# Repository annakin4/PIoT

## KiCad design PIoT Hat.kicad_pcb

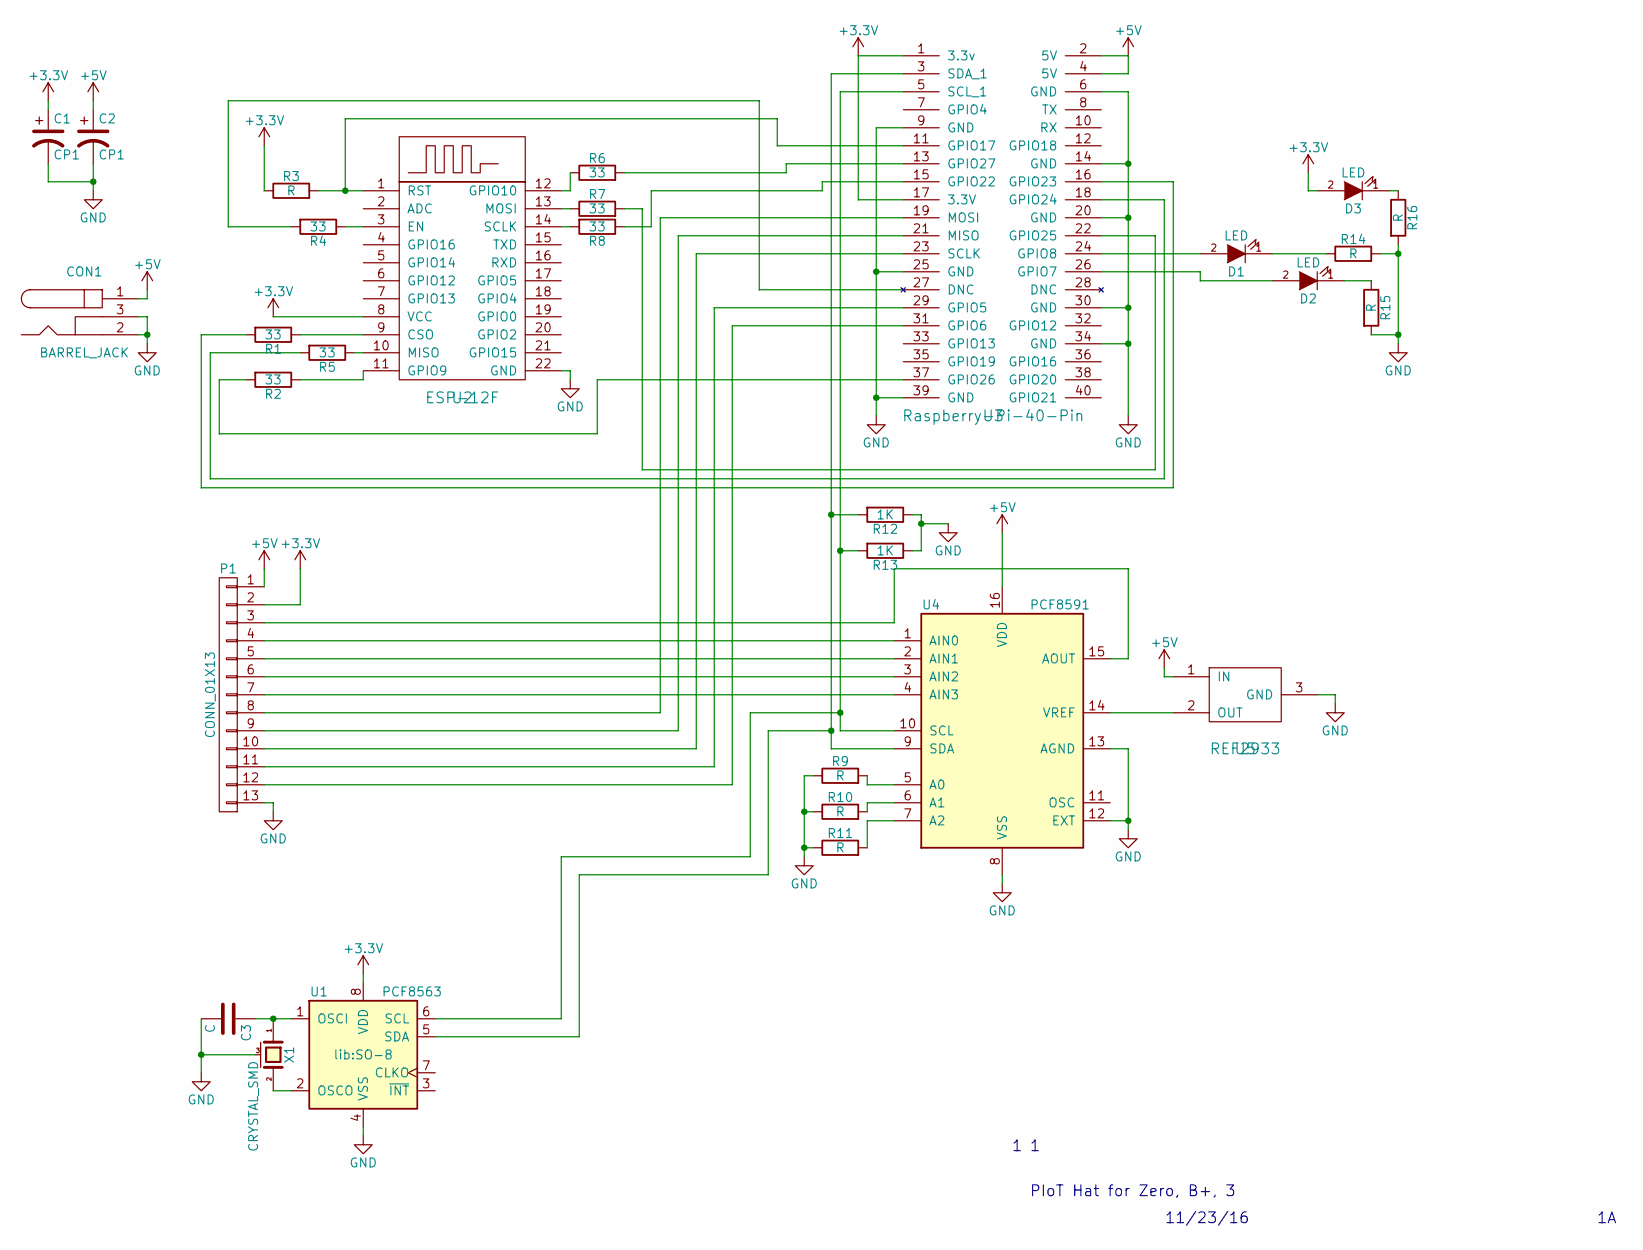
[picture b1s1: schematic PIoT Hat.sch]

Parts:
C1, C2: CP1; c_elec_4x5.7
C3: C; C_0805
CON1: BARREL_JACK
D1, D2, D3: LED; LED_0805
P1: CONN_01X13; Molex_KK-6410-13_13x2.54mm_Straight
R1, R2, R4, R5, R6, R7, R8: 33; R_0805
R3, R9, R10, R11, R14, R15, R16: R; R_0805
R12, R13: 1K; R_0805
U1: PCF8563; SO-8
U2: ESP-12F
U3: Raspberry-Pi-40-Pin; 40-Pin_Raspberry_Pi
U4: PCF8591; SO16
U5: REF2933; SOT-23
X1: CRYSTAL_SMD; Crystal_SMD_Micro-Crystal_MS1V-T1K

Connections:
+3V3: C1.1, D3.2 (A), P1.2, R3.1, U1.8 (VDD), U2.8 (VCC), U3.1 (3.3v), U3.17 (3.3V)
+5V: C2.1, CON1.1, P1.1, U3.2 (5V), U3.4 (5V), U4.16 (VDD), U5.1 (IN)
GND: C1.2, C2.2, C3.2, CON1.2, CON1.3, P1.13, R9.1, R10.1, R11.1, R12.1, R13.1, R14.2, R15.2, R16.2, U1.4 (VSS), U2.22 (GND), U3.6 (GND), U3.9 (GND), U3.14 (GND), U3.20 (GND), U3.25 (GND), U3.30 (GND), U3.34 (GND), U3.39 (GND), U4.8 (VSS), U4.12 (EXT), U4.13 (AGND), U5.3 (GND), X1.3 (case)
unnamed: C3.1, U1.1 (OSCI), X1.1
unnamed: D1.1 (K), R14.1
unnamed: D1.2 (A), U3.24 (GPIO8)
unnamed: D2.1 (K), R15.1
unnamed: D2.2 (A), U3.26 (GPIO7)
unnamed: D3.1 (K), R16.1
unnamed: P1.3, U4.15 (AOUT)
unnamed: P1.4, U4.1 (AIN0)
unnamed: P1.5, U4.2 (AIN1)
unnamed: P1.6, U4.3 (AIN2)
unnamed: P1.7, U4.4 (AIN3)
unnamed: P1.8, U3.19 (MOSI)
unnamed: P1.9, U3.21 (MISO)
unnamed: P1.10, U3.23 (SCLK)
unnamed: P1.11, U3.29 (GPIO5)
unnamed: P1.12, U3.31 (GPIO6)
unnamed: R1.1, U2.9 (CSO)
unnamed: R1.2, U3.16 (GPIO23)
unnamed: R2.1, U2.11 (GPIO9)
unnamed: R2.2, U3.37 (GPIO26)
unnamed: R3.2, U2.1 (RST), U3.11 (GPIO17)
unnamed: R4.1, U2.3 (EN)
unnamed: R4.2, U3.27 (DNC)
unnamed: R5.1, U2.10 (MISO)
unnamed: R5.2, U3.18 (GPIO24)
unnamed: R6.1, U2.12 (GPIO10)
unnamed: R6.2, U3.13 (GPIO27)
unnamed: R7.1, U2.13 (MOSI)
unnamed: R7.2, U3.22 (GPIO25)
unnamed: R8.1, U3.15 (GPIO22)
unnamed: R8.2, U2.14 (SCLK)
unnamed: R9.2, U4.5 (A0)
unnamed: R10.2, U4.6 (A1)
unnamed: R11.2, U4.7 (A2)
unnamed: R12.2, U1.5 (SDA), U3.3 (SDA_1), U4.9 (SDA)
unnamed: R13.2, U1.6 (SCL), U3.5 (SCL_1), U4.10 (SCL)
unnamed: U1.2 (OSCO), X1.2
unnamed: U4.14 (VREF), U5.2 (OUT)

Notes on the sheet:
PIoT Hat for Zero, B+, 3
11/23/16

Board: 2 copper layers, 30 parts (5 on the bottom side), 41 nets, no tracks yet.

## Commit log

2016-11-25 :boom::camel: Added .gitattributes & .gitignore files
2016-11-25 Finished Schematic of A1
